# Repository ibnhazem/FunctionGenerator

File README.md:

# FunctionGenerator
Function Generator. AC signal generator using OPamps

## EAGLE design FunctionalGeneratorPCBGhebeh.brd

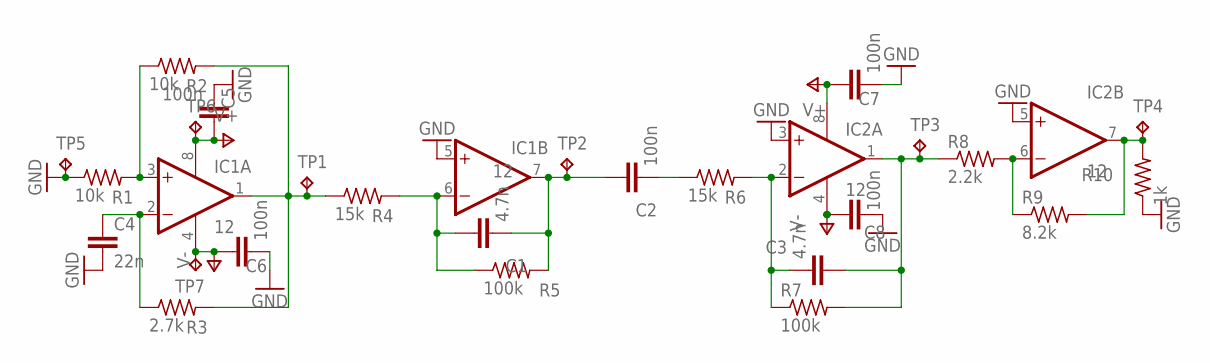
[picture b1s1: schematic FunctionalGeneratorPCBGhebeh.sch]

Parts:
C1, C3: 4.7n; C5B3
C2, C5, C6, C7, C8: 100n; C5B3
C4: 22n; C5B3
IC1, IC2: 12; DIL08
R1, R2: 10k; 0309/10
R3: 2.7k; 0309/10
R4, R6: 15k; 0309/10
R5, R7: 100k; 0309/10
R8: 2.2k; 0309/10
R9: 8.2k; 0309/10
R10: 1k; 0309/10
TP1, TP2, TP3, TP4, TP5, TP6, TP7: TPPAD1-13Y; P1-13Y

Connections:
GND: C4.2, C5.2, C6.2, C7.2, C8.1, IC1.5 (+IN), IC2.3 (+IN), IC2.5 (+IN), R1.1, R10.1, TP5.TP
unnamed: IC1.3 (+IN), R1.2, R2.1
unnamed: C4.1, IC1.2 (-IN), R3.1
unnamed: IC1.1 (OUT), R2.2, R3.2, R4.1, TP1.TP
unnamed: C1.1, IC1.6 (-IN), R4.2, R5.1
unnamed: C1.2, C2.1, IC1.7 (OUT), R5.2, TP2.TP
unnamed: C3.1, IC2.2 (-IN), R6.2, R7.1
unnamed: C2.2, R6.1
unnamed: C3.2, IC2.1 (OUT), R7.2, R8.1, TP3.TP
unnamed: IC2.6 (-IN), R8.2, R9.1
unnamed: IC2.7 (OUT), R9.2, R10.2, TP4.TP
V+: C5.1, C7.1, IC1.8 (V+), IC2.8 (V+), TP6.TP
V-: C6.1, C8.2, IC1.4 (V-), IC2.4 (V-), TP7.TP

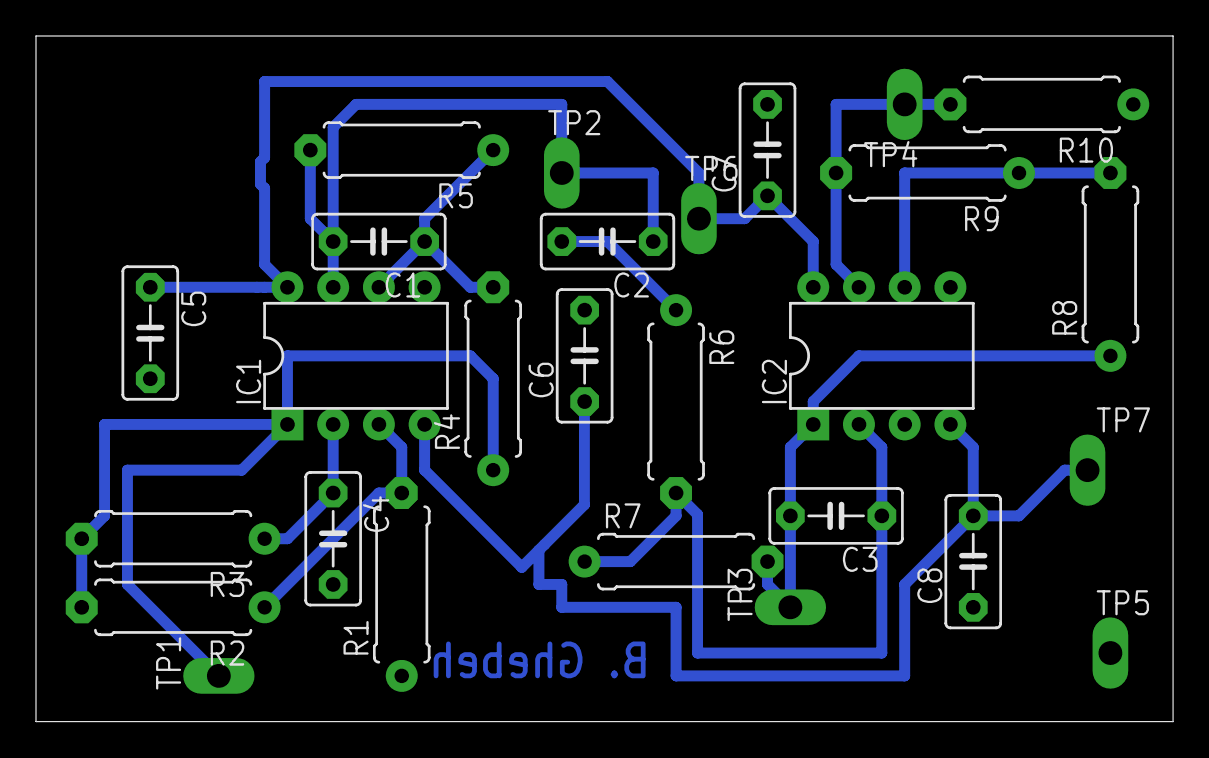
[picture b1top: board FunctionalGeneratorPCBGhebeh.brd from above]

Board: 2 copper layers, 63.2 x 38.1 mm, 27 parts (0 on the bottom side), 13 nets.

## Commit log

2023-07-13 Final function generator files
2023-07-13 Not needed
    There is a project report detailing the project's journey and description
